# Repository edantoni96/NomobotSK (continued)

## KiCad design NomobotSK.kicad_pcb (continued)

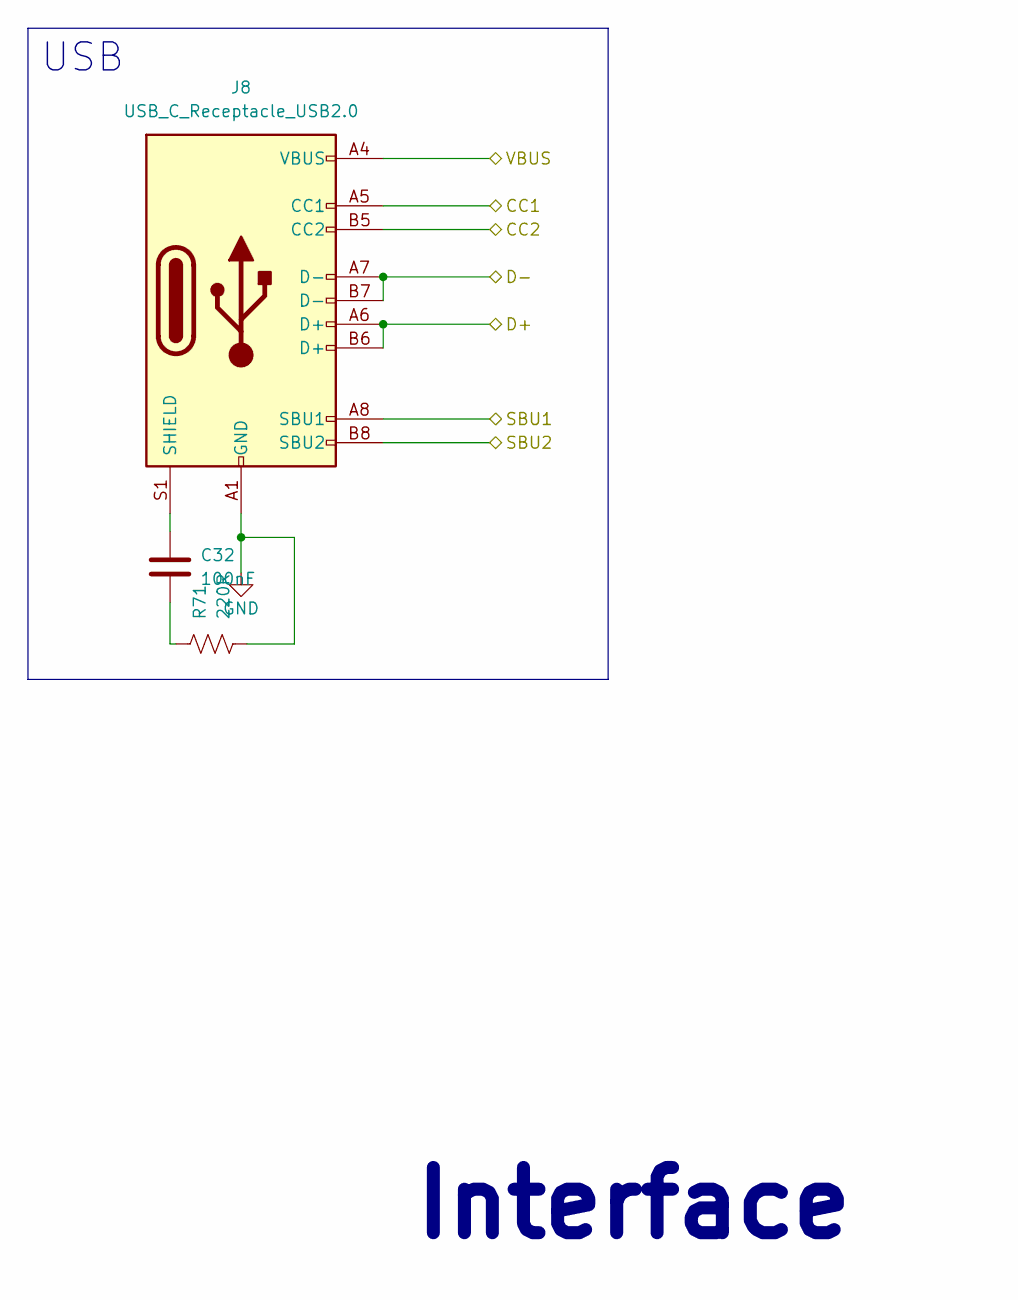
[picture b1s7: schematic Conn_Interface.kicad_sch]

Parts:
C32: 100nF; C_0603_1608Metric
J8: USB_C_Receptacle_USB2.0; USB_C_Receptacle_HRO_TYPE-C-31-M-12
R71: 220R; R_0603_1608Metric

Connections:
/CONNECTOR/CC1: J8.A5 (CC1); also elsewhere on the board
/CONNECTOR/CC2: J8.B5 (CC2); also elsewhere on the board
/CONNECTOR/D+: J8.A6 (D+), J8.B6 (D+); also elsewhere on the board
/CONNECTOR/D-: J8.A7 (D-), J8.B7 (D-); also elsewhere on the board
/CONNECTOR/SBU1: J8.A8 (SBU1)
/CONNECTOR/SBU2: J8.B8 (SBU2)
/CONNECTOR/VBUS: J8.A4 (VBUS), J8.A9 (VBUS), J8.B4 (VBUS), J8.B9 (VBUS); also elsewhere on the board
GND: J8.A1 (GND), J8.A12 (GND), J8.B1 (GND), J8.B12 (GND), R71.2; also elsewhere on the board
unnamed: C32.2, R71.1
unnamed: C32.1, J8.S1 (SHIELD)

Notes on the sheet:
Interface
USB

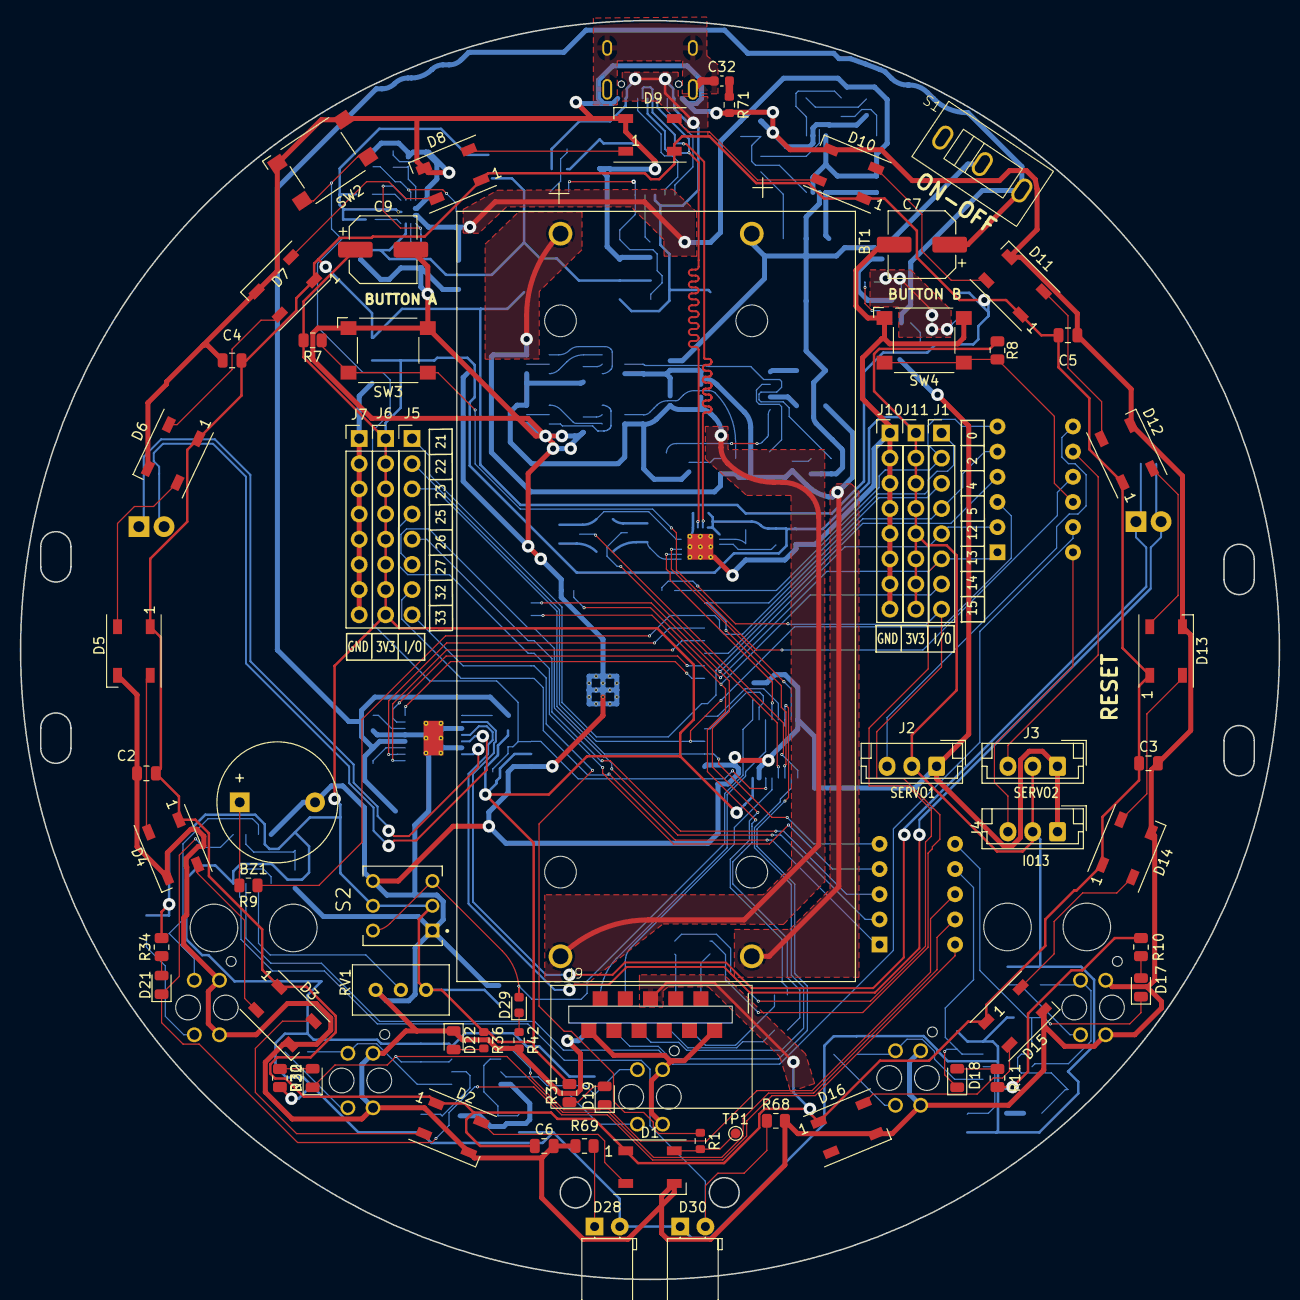
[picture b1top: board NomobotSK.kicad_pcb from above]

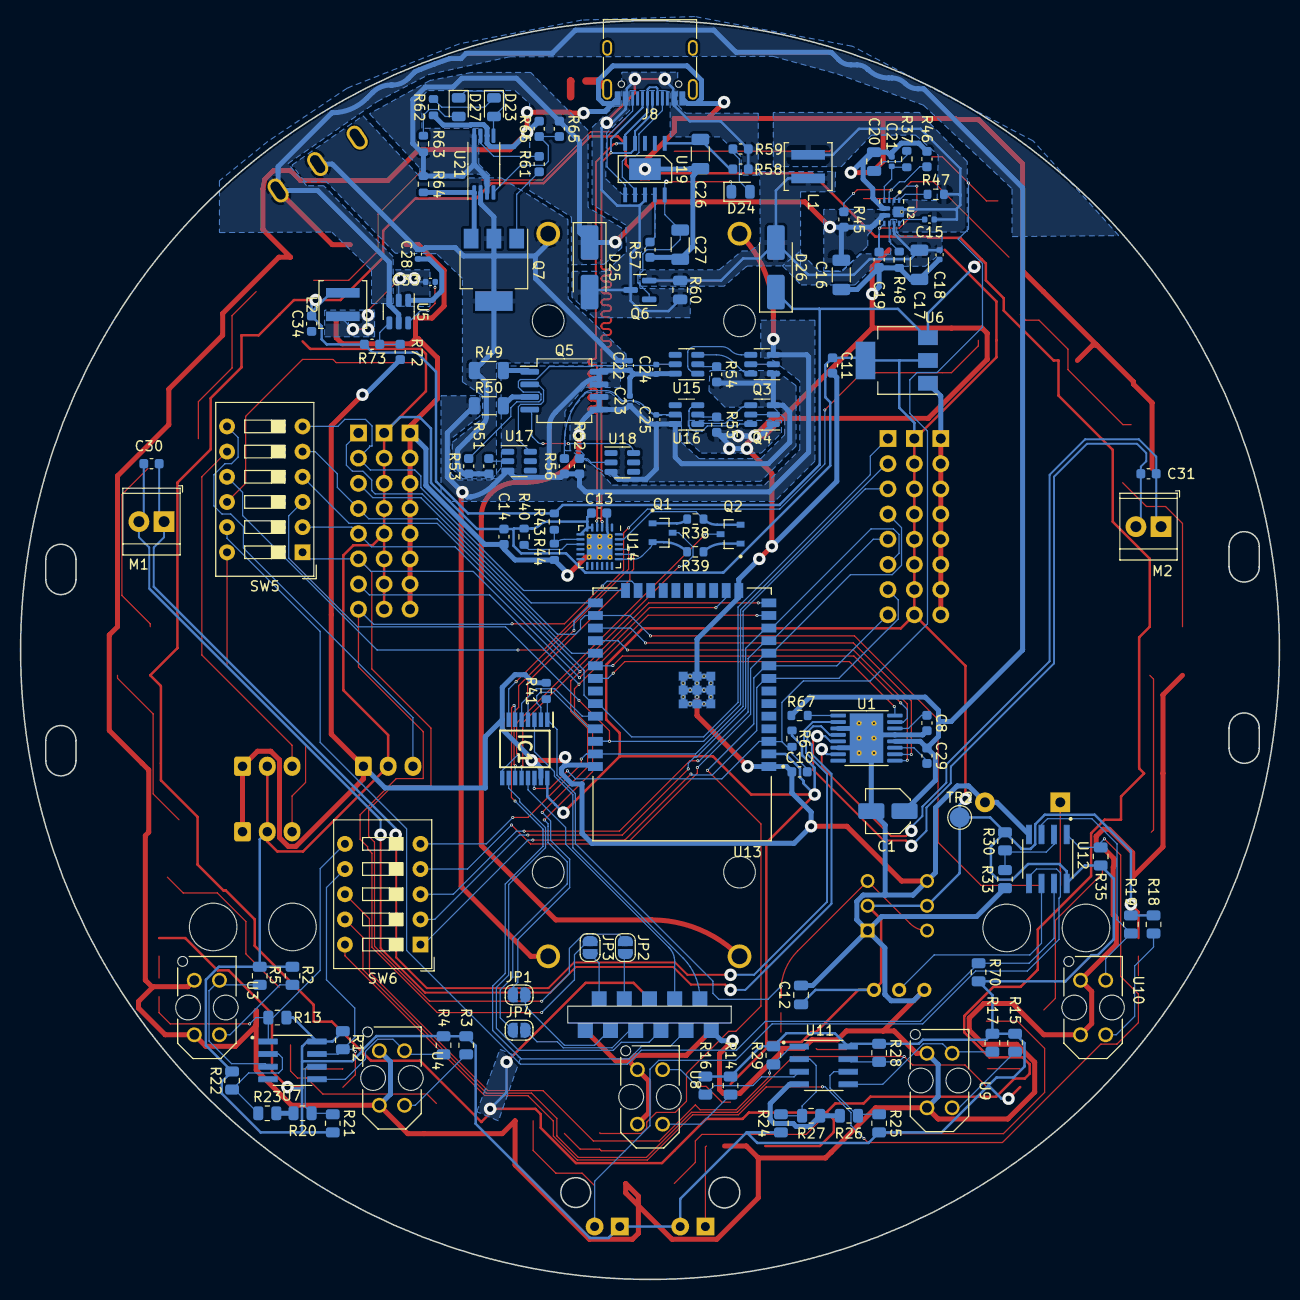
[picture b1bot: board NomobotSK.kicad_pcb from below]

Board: 2 copper layers, 127.0 x 127.0 mm, 196 parts (130 on the bottom side), 156 nets.

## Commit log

2023-12-09 v1 push
2023-12-09 Add output files
2023-12-09 Add top picture
2023-12-09 add tester instruction
2023-12-09 fix pdf view
2023-12-09 fix readme
2024-01-06 change design of comparator
2024-02-10 routing done
